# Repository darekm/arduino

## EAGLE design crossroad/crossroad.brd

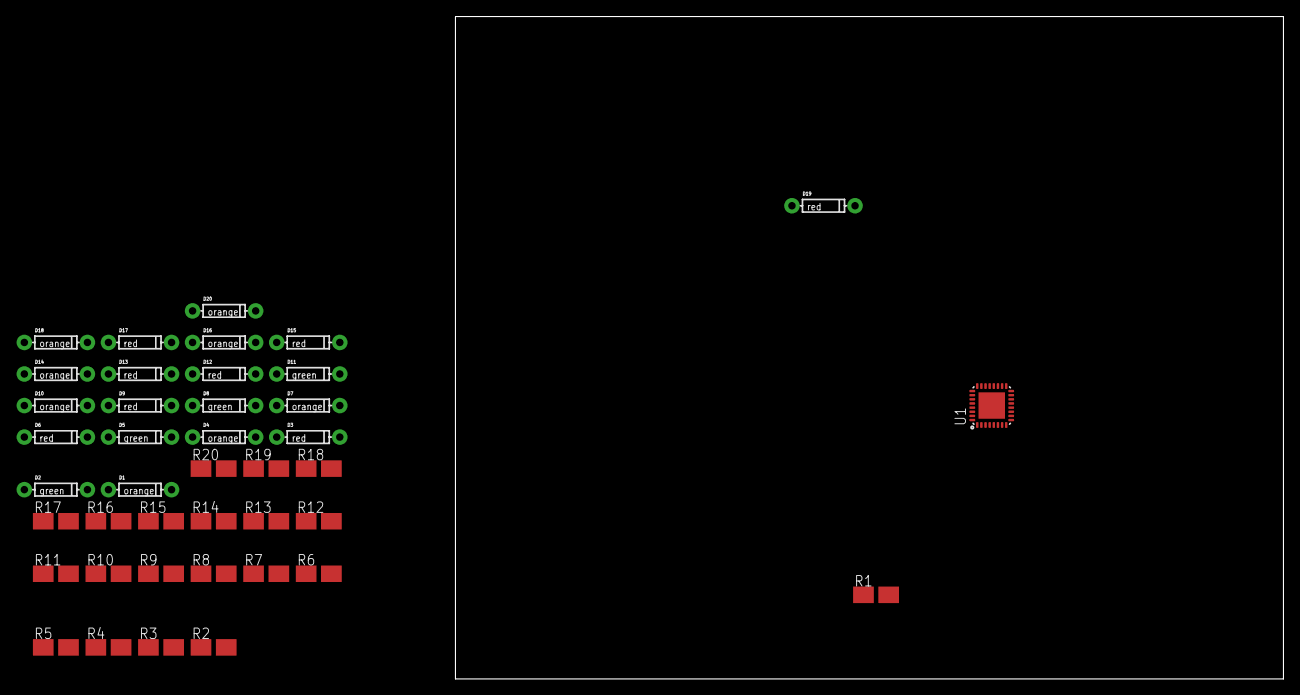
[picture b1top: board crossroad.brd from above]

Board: 2 copper layers, 100.0 x 80.0 mm, 41 parts (0 on the bottom side), 35 nets, no tracks yet.

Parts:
D1, D4, D7, D10, D14, D16, D18, D20: orange; DIODE-1N4148
D2, D5, D8, D11: green; DIODE-1N4148
D3, D6, D9, D12, D13, D15, D17, D19: red; DIODE-1N4148
R1, R2, R3, R4, R5, R6, R7, R8, R9, R10, R11, R12, R13, R14, R15, R16, R17, R18, R19, R20: 300; SMK
U1: MLF32-PAD

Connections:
HOR_GREEN: D2.C, D5.C, U1.25
HOR_ORANGE: D1.C, D4.C, U1.24
HOR_RED: D3.C, D6.C, U1.23
HOR_WALKWAY_GREEN: D14.C, D16.C, U1.31
HOR_WALKWAY_RED: D13.C, D15.C, U1.30
unnamed: D3.A, R1.1
unnamed: D1.A, R2.1
unnamed: D2.A, R3.1
unnamed: D6.A, R4.1
unnamed: D4.A, R5.1
unnamed: D5.A, R6.1
unnamed: D9.A, R7.1
unnamed: D7.A, R8.1
unnamed: D8.A, R9.1
unnamed: D12.A, R10.1
unnamed: D10.A, R11.1
unnamed: D11.A, R12.1
unnamed: D13.A, R13.1
unnamed: D14.A, R14.1
unnamed: R13.2, R14.2
unnamed: D15.A, R15.1
unnamed: D16.A, R16.1
unnamed: R15.2, R16.2
unnamed: D17.A, R17.1
unnamed: D18.A, R18.1
unnamed: R17.2, R18.2
unnamed: D19.A, R19.1
unnamed: D20.A, R20.1
unnamed: R19.2, R20.2
VCC: R1.2, R2.2, R3.2, R4.2, R5.2, R6.2, R7.2, R8.2, R9.2, R10.2, R11.2, R12.2, U1.4
VER_GREEN: D8.C, D11.C, U1.28
VER_ORANGE: D7.C, D10.C, U1.27
VER_RED: D9.C, D12.C, U1.26
VER_WALKWAY_GREEN: D18.C, D20.C, U1.22
VER_WALKWAY_RED: D17.C, D19.C, U1.19

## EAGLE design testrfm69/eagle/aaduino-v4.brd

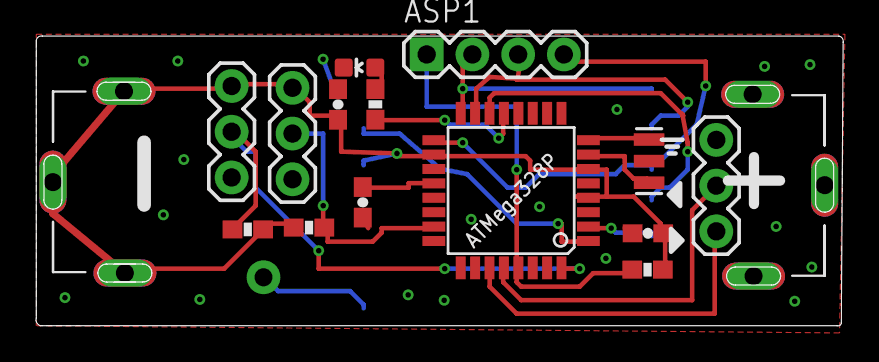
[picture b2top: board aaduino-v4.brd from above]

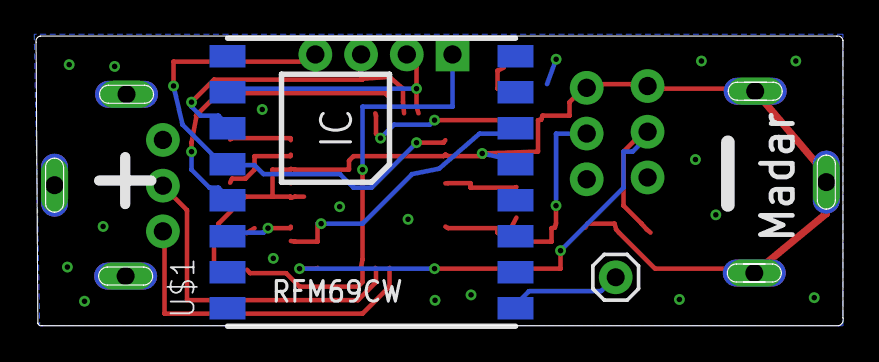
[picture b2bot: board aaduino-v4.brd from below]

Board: 2 copper layers, 44.8 x 16.1 mm, 18 parts (2 on the bottom side), 19 nets.

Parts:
ANT: M01PTH; 1X01
ASP1: 1X04
C1, C2, C3: 0.1uF; 0603-CAP
J1: KEYSTONE-629; KEYSTONE_AA_AAA_BATTERY_TERMINAL-629
J2: KEYSTONE-637; KEYSTONE_AA_AAA_BATTERY_TERMINAL-637
JP1, JP2, JP3: 1X03
LED1: green; LED-0603
R1: 10k; 0603-RES
R2: 1k8; 0603-RES
R3, R4: 4k7; 0603-RES
U1: ATMEGA328P; TQFP32-08
U3: RESONATOR_16MHZ; RESONATOR_SMD
U$1: RFM69HCW-S2; HOPE-RF-16

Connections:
ACT: R2.2, U1.13
ADC0: JP3.2, R4.2, U1.23
GND: C1.2, C2.2, C3.2, J1.GND@1, J1.GND@2, J1.GND@3, JP1.1, JP2.1, JP3.1, LED1.C, U1.3, U1.5, U1.21, U3.2, U$1.GND1, U$1.GND2, U$1.GND3
MISO: ASP1.2, U1.16, U$1.MISO
MOSI: ASP1.3, U1.15, U$1.MOSI
unnamed: LED1.A, R2.1
unnamed: ANT.1, U$1.ANT
unnamed: C3.1, U1.20
unnamed: U1.7, U3.1
unnamed: U1.8, U3.3
RESET: ASP1.1, R1.2, U1.29
RFM_IRQ: U1.1, U$1.DIO0
RFM_RST: U1.2, U$1.RESET
SCK: ASP1.4, U1.17, U$1.SCK
SDA: JP1.3, U1.27
SDL: JP1.2, U1.28
SEL: U1.14, U$1.NSS
VCC: C1.1, C2.1, J2.VCC@1, J2.VCC@2, J2.VCC@3, JP2.3, JP3.3, R1.1, R3.1, R4.1, U1.4, U1.6, U1.18, U$1.3.3V
WIRED: JP2.2, R3.2, U1.32

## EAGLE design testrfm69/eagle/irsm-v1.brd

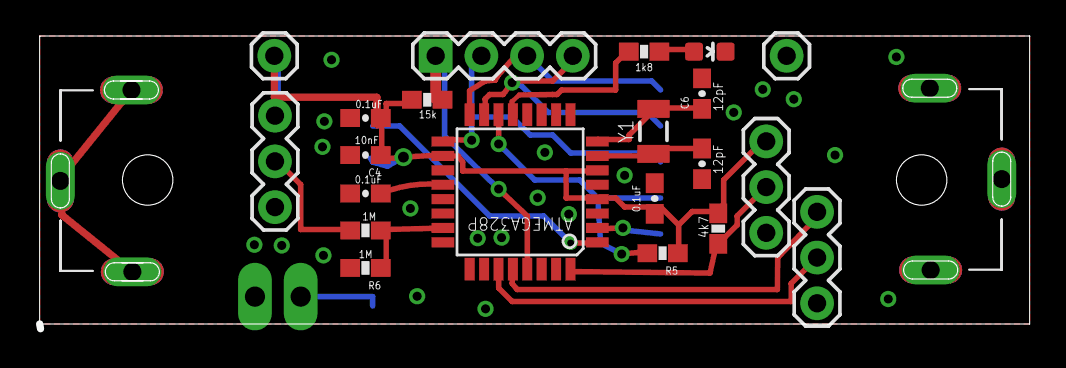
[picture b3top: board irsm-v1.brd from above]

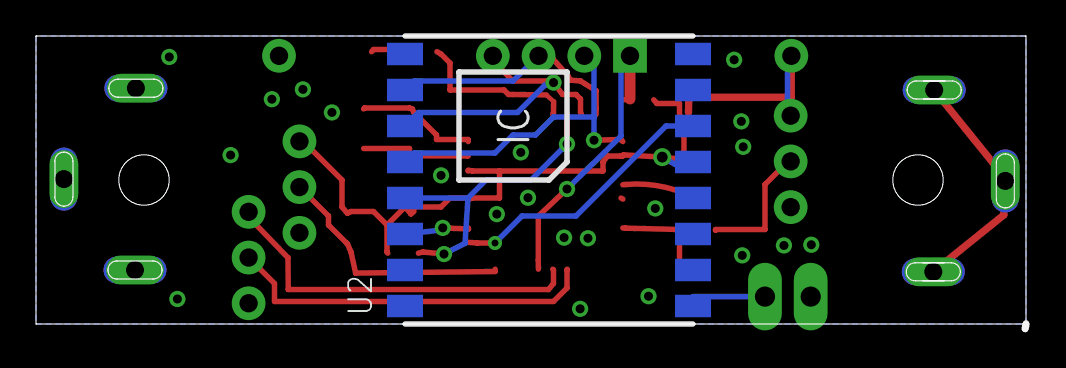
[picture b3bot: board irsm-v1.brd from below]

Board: 2 copper layers, 55.0 x 16.0 mm, 25 parts (2 on the bottom side), 20 nets.

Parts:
ANT: 1X02_LONGPADS
ASP1: 1X04
C1, C2, C3: 0.1uF; 0603-CAP
C4: 10nF; 0603-CAP
C5, C6: 12pF; 0603-CAP
J1: KEYSTONE-629; KEYSTONE_AA_AAA_BATTERY_TERMINAL-629
J2: KEYSTONE-637; KEYSTONE_AA_AAA_BATTERY_TERMINAL-637
J3, J4: 1X01
JP1, JP2, JP3: 1X03
LED1: green; LED-0603
R1, R5: 15k; 0603-RES
R2: 1k8; 0603-RES
R3: 4k7; 0603-RES
R4, R6: 1M; 0603-RES
U1: ATMEGA328P; TQFP32-08
U2: RFM69HCW-S2; HOPE-RF-16
Y1: 32.768kHz; CRYSTAL-SMD-3.2X1.5MM

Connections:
ACT: R2.2, U1.13
ADC0: R4.2, R6.1, U1.23
GND: ANT.2, C1.2, C2.2, C3.2, C4.2, C5.2, C6.2, J1.GND@1, J1.GND@2, J1.GND@3, J4.1, JP1.1, JP2.1, JP3.1, LED1.C, R6.2, U1.3, U1.5, U1.21, U2.GND1, U2.GND2, U2.GND3
MISO: ASP1.3, U1.16, U2.MISO
MOSI: ASP1.4, U1.15, U2.MOSI
unnamed: LED1.A, R2.1
unnamed: JP3.2, R4.1
unnamed: ANT.1, U2.ANT
unnamed: C3.1, U1.20
unnamed: C5.1, U1.7, Y1.P$1
unnamed: C6.1, U1.8, Y1.P$2
RESET: ASP1.1, R1.2, U1.29
RFM_IRQ: U1.1, U2.DIO0
RFM_RST: U1.2, U2.RESET
SCK: ASP1.2, U1.17, U2.SCK
SDA: JP1.2, U1.27
SDL: JP1.3, U1.28
SEL: R5.2, U1.14, U2.NSS
VCC: C1.1, C2.1, C4.1, J2.VCC@1, J2.VCC@2, J2.VCC@3, J3.1, JP2.3, JP3.3, R1.1, R3.1, R5.1, U1.4, U1.6, U1.18, U2.3.3V
WIRED: JP2.2, R3.2, U1.32

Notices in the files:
parts and their libraries:
SparkFun-DiscreteSemi: Licensing: Creative Commons ShareAlike 4.0 International - https://creativecommons.org/licenses/by-sa/4.0
icmi-custom-parts: ICMI Custom Parts for EAGLE by Hendrik Busch is licensed under a Creative Commons
Attribution-NonCommercial-ShareAlike 3.0 Germany License.
